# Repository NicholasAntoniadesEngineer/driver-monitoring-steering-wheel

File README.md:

# ECG Steering wheel
This folder contains all the code and schematics required to assemble and run the prototype Steering wheel and it's individual elements. 

**Fresh Installation**
1. Flash new RaspberryPi image
    - Using Raspberry Pi Imager flash the latest version of RASPBERRY PI OS LITE (32-BIT) onto the SD-Card that will hold the Pis OS.
  
    - Once complete insert into Pi and power it up.
        - Username: pi
        - Password: raspberry

2. Initialise network connections
    - Enable SSH:
        - sudo raspi-config,
            - In interface options enable SSH

    - Connect to the wifi network, tutorial found in the following link.
       (https://desertbot.io/blog/headless-raspberry-pi-4-ssh-wifi-setup)
    
2. Download the repository from git.
    - sudo apt update
    - sudo apt upgrade
    - set the ip address of the Pi
    - sudo apt install git
    - sudo apt clone https://github.com/NicholasAntoniadesEngineer/ECG-Steering-Wheel.git
    
3. Install I2C and SPI dependencies
    - Enable I2C,SPI:
        - run sudo raspi-config,
            - In interface options enable SPI,I2C,Serial
    - sudo apt install python
    - sudo apt install pip
    - sudo pip install spidev
    - pip3 install RPi.GPIO
    - pip3 install spidev
    - pip3 install pygame
    - sudo apt-get install libsdl-ttf2.0-0
    - Initialization of multiple SPI channels, tutorial found in the following link.
      (https://raspberrypi.stackexchange.com/questions/61430/i-want-to-use-spi0-and-spi1-at-the-same-time)

4. Install GPS libraries in I2C/PA1010D
    - sudo install.sh
    - sudo pip install smbus0
    
6. Install NFC hat libraries
    - pip install serial
    - pip3 install serial

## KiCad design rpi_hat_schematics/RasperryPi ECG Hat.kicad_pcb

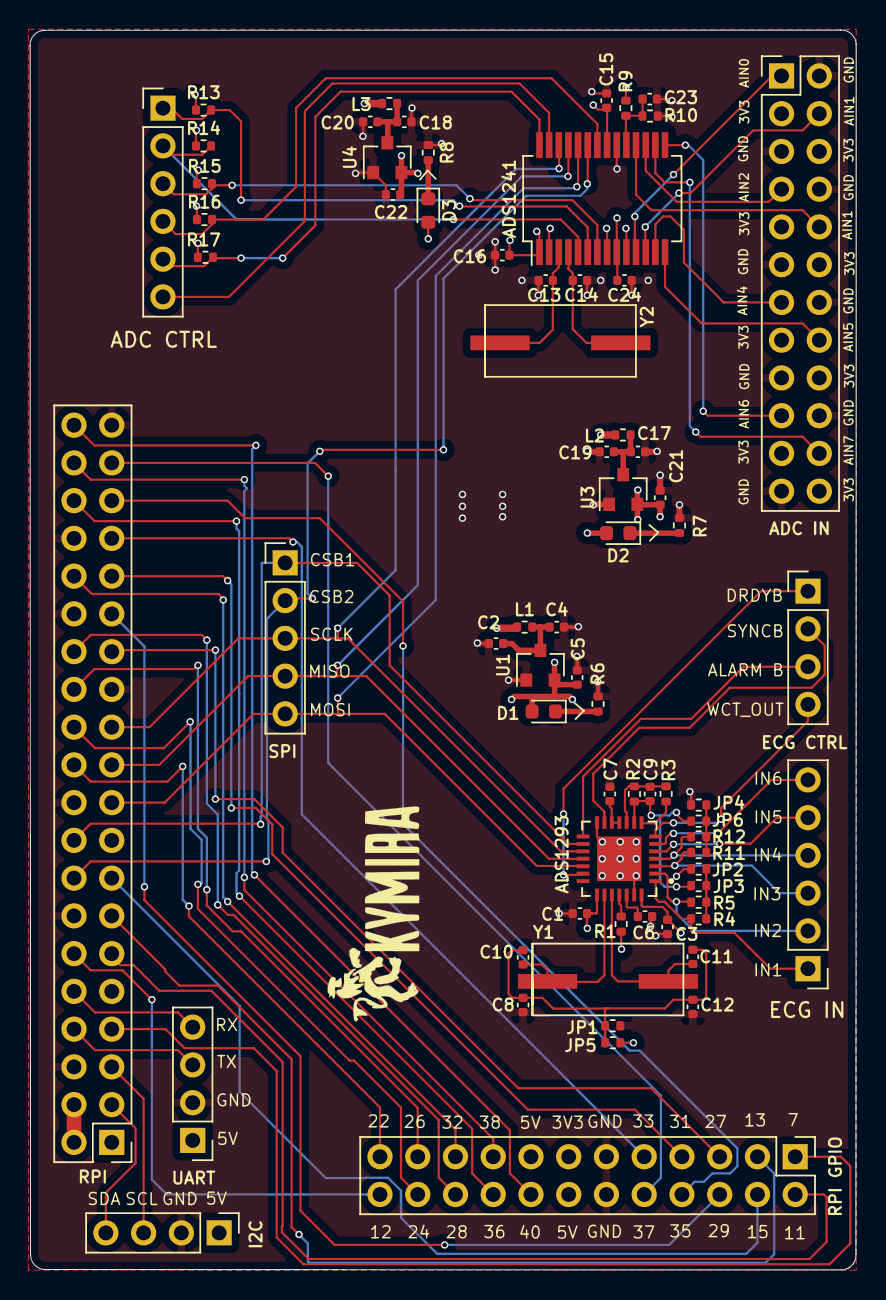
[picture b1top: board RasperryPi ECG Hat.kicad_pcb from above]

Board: 4 copper layers, 55.6 x 83.4 mm, 69 parts (0 on the bottom side), 78 nets.

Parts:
ADC CTRL: ADC Control; PinHeader_1x06_P2.54mm_Vertical
ADC IN: ADC Input; PinHeader_2x12_P2.54mm_Vertical
ADS1241: ADS1241; SSOP-28_5.3x10.2mm_P0.65mm
ADS1293: ADS1293; WQFN 28
C1, C3, C7, C8, C12, C15, C16, C23, C24: 100n; C_0402_1005Metric
C2, C17, C18: 10u; C_0402_1005Metric
C4, C5, C19, C20, C21, C22: 4.7u; C_0402_1005Metric
C6: 1u; C_0402_1005Metric
C9: 1n; C_0402_1005Metric
C10, C11, C13, C14: 18p; C_0402_1005Metric
D1, D2, D3: LED
ECG CTRL: ECG Control; PinHeader_1x04_P2.54mm_Vertical
ECG IN: ECG Input; PinHeader_1x06_P2.54mm_Vertical
I2C: I2C; PinHeader_1x04_P2.54mm_Vertical
JP1, JP2, JP3, JP4, JP5, JP6: Jumper; R_0402_1005Metric
L1, L2, L3: INDUCTOR; R_0402_1005Metric
R1: 1M; R_0402_1005Metric
R2, R4, R5, R11, R12: 10M; R_0402_1005Metric
R3, R9, R10, R13, R14, R15, R16, R17: 10k; R_0402_1005Metric
R6, R7, R8: 600; R_0402_1005Metric
RPI: Raspberry_Pi_4; PinHeader_2x20_P2.54mm_Vertical
RPI GPIO: Extra pins; PinHeader_2x12_P2.54mm_Vertical
SPI: SPI; PinHeader_1x05_P2.54mm_Vertical
U1, U3, U4: MCP1703A; SOT-23
UART: UART; PinHeader_1x04_P2.54mm_Vertical
Y1, Y2: 4.096; SMD_Crystal_2_pin_11.3_4.5

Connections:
3V3: RPI.1, RPI GPIO.13
5V: I2C.1, L1.1, L2.1, L3.1, RPI.2, RPI.4, RPI GPIO.14, RPI GPIO.15, UART.1
7: RPI.7, RPI GPIO.1
11: RPI.11, RPI GPIO.2
12: RPI.12, RPI GPIO.24
13: RPI.13, RPI GPIO.3
15: RPI.15, RPI GPIO.4
22: RPI.22, RPI GPIO.23
24: RPI.24, RPI GPIO.22
26: RPI.26, RPI GPIO.21
27: RPI.27, RPI GPIO.5
28: RPI.28, RPI GPIO.20
29: RPI.29, RPI GPIO.6
31: RPI.31, RPI GPIO.7
32: RPI.32, RPI GPIO.19
33: RPI.33, RPI GPIO.9
35: RPI.35, RPI GPIO.8
36: RPI.36, RPI GPIO.18
37: RPI.37, RPI GPIO.10
38: RPI.38, RPI GPIO.17
40: RPI.40, RPI GPIO.16
ADC_3v3: ADS1241.1, ADS1241.9, ADS1241.21, C15.1, C16.1, C22.1, C24.1, D3.1, R9.1, R13.1, R14.1, R15.1, R16.1, R17.1, U4.2
AIN0: ADC IN.1, ADS1241.11
AIN1: ADC IN.4, ADS1241.12
AIN2: ADC IN.7, ADS1241.17
AIN3: ADC IN.10, ADS1241.18
AIN4: ADC IN.13, ADS1241.13
AIN5: ADC IN.16, ADS1241.14
AIN6: ADC IN.19, ADS1241.15
AIN7: ADC IN.22, ADS1241.16
ALARMB: ADS1293.15, ECG CTRL.3
BUFEN: ADC CTRL.5, ADS1241.28, R17.2
CSB1: ADS1293.16, RPI.18, SPI.1
CSB2: ADS1241.23, RPI.16, SPI.2
DRDY: ADC CTRL.6, ADS1241.27
DRDYB: ADS1293.20, ECG CTRL.1
ECG_3v3: ADS1293.22, ADS1293.28, C1.1, C3.1, C5.1, D1.1, JP5.2, R1.1, U1.2
Earth: ADC IN.2, ADC IN.5, ADC IN.8, ADC IN.11, ADC IN.14, ADC IN.17, ADC IN.20, ADC IN.23, ADS1241.2, ADS1241.8, ADS1241.10, ADS1241.20, ADS1293.14, ADS1293.27, ADS1293.29, C1.2, C2.2, C3.2, C4.2, C5.2, C6.2, C7.2, C8.2, C12.2, C13.2, C14.2, C15.2, C16.2, C17.2, C18.2, C19.2, C20.2, C21.2, C22.2, C23.2, C24.2, I2C.2, JP1.1, JP2.1, JP4.1, R6.2, R7.2, R8.2, R10.2, RPI.6, RPI.9, RPI.14, RPI.20, RPI.25, RPI.30, RPI.34, RPI.39, RPI GPIO.11, RPI GPIO.12, U1.1, U3.1, U4.1, UART.2
I2C1_SCL: I2C.3, RPI.5
I2C1_SDA: I2C.4, RPI.3
IN1: ADS1293.1, ECG IN.1, R4.2
IN2: ADS1293.2, ECG IN.2, R5.2
IN3: ADS1293.3, ECG IN.3, R11.2
IN4: ADS1293.4, ECG IN.4, R12.2
IN5: ADS1293.5, ECG IN.5
IN6: ADS1293.6, ECG IN.6
MISO: ADS1241.25, ADS1293.18, RPI.21, SPI.4
MOSI: ADS1241.24, ADS1293.19, RPI.19, SPI.5
unnamed: C2.1, C4.1, L1.2, U1.3
unnamed: ADS1293.26, C6.1
unnamed: ADS1293.11, ADS1293.12, C7.1
unnamed: ADS1293.10, C9.2, R2.2, R3.2
unnamed: C8.1, C10.1, C11.1, C12.1, JP1.2, JP5.1
unnamed: ADS1293.23, C10.2, Y1.1
unnamed: ADS1293.24, C11.2, Y1.2
unnamed: ADS1241.3, C13.1, Y2.1
unnamed: ADS1241.4, C14.1, Y2.2
unnamed: C17.1, C19.1, L2.2, U3.3
unnamed: C18.1, C20.1, L3.2, U4.3
unnamed: ADS1241.19, C23.1, R9.2, R10.1
unnamed: D1.2, R6.1
unnamed: D2.2, R7.1
unnamed: D3.2, R8.1
unnamed: JP2.2, JP3.1, R4.1, R5.1
unnamed: JP4.2, JP6.1, R11.1, R12.1
unnamed: ADS1293.25, R1.2
unnamed: ADS1293.8, R3.1
POL: ADC CTRL.4, ADS1241.22, R16.2
RLDOUT: ADS1293.9, C9.1, JP3.2, JP6.2, R2.1
SCLK: ADS1241.26, ADS1293.17, RPI.23, SPI.3
SYNCB: ADS1293.13, ECG CTRL.2
Strain_3v3: ADC IN.3, ADC IN.6, ADC IN.9, ADC IN.12, ADC IN.15, ADC IN.18, ADC IN.21, ADC IN.24, C21.1, D2.1, U3.2
UART_RX: RPI.10, UART.4
UART_TX: RPI.8, UART.3
WCT_OUT: ADS1293.7, ECG CTRL.4
~DSYNC: ADC CTRL.1, ADS1241.6, R13.2
~PDWN: ADC CTRL.3, ADS1241.7, R15.2
~RESET: ADC CTRL.2, ADS1241.5, R14.2

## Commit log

2022-02-09 Initial code upload
2022-02-09 Recipe for fresh installation.
2022-02-09 Including functions of each folder
2022-02-09 Including research and organising folders
2022-02-09 Including schematic
2022-02-10 Running code from the command line
2022-07-28 Videos of the ECG and Pressure sensor in action
2024-11-01 Rename README.md to readme.md
2024-11-04 workinf
2024-11-08 Rename ECG_and_Grip_Force.py to ecg_and_grip_force.py
2024-11-08 renaming and organising
2024-11-08 Rename Videos.zip to videos.zip
2024-11-09 cleaning things up
2025-01-15 Organise code base
2025-01-15 refactoring code
2025-01-15 add images
2025-01-15 Add video and update readme
2025-01-15 rename folder
2025-01-15 renaming files
2025-01-15 organising files
2025-01-15 moving files
2025-01-15 Rename RasperryPi ECG Hat.jpg to rpi_ecg_adc_pcb.jpg
2025-01-15 moving images around
2025-01-15 adding schematic
2025-01-15 add .pdf
2025-01-16 clearing up repo
2025-01-16 moving files around
2025-01-22 compress schematics to save sapce
